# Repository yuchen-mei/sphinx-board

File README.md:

# Sphinx ASIC Test Board

Sphinx is a test board for voltage, frequency, power, and energy-efficiency characterization of a TSMC N7 ASIC. The nominal operating point is 0.75 V core supply, approximately 5 W during kernel execution, and a target clock frequency of 1 GHz. A local programmable regulator, distributed decoupling, and differential feedback at the socket provide the board-level power delivery path.

Hardware: **V2**. This package contains the current schematic project, local KiCad libraries, BOM, schematic exports, and design documentation. The [Pico controller source](../controller/README.md) is maintained alongside this package. There is no V2 PCB, completed host test application, or board measurement evidence in the current repository.

## Design files

Open [schematic/sphinx_power_v2.kicad_pro](schematic/sphinx_power_v2.kicad_pro) in KiCad 10.

| File | Contents |
|---|---|
| [Schematic PDF](schematic/exports/sphinx_power_v2.pdf) | Eleven schematic sheets |
| [XML netlist](schematic/exports/sphinx_power_v2.net.xml) | Component connections |
| [Parts catalog](schematic/bom/parts_catalog.json) | Exact parts, assembly options, and application notes |
| [Purchase list](schematic/bom/BUY_LIST.csv) | Quantities for five boards and spares |
| [Component list](schematic/bom/component_list.csv) | Schematic components and fields |
| [Documentation](docs/README.md) | Requirements, interfaces, layout constraints, and verification |
| [Maintenance](CONTRIBUTING.md) | Editing and validation procedure |

## Operating scope

The core regulator covers 0.30–1.20 V. The lower end supports low-voltage energy-efficiency measurements. The conservative continuous-current design target is 10 A. I/O operates at a fixed 1.8 V. The supported operating region is determined experimentally for each device and workload; the regulator range does not define an ASIC voltage rating.

The board uses explicit `SET` / `ON` commands to program and enable the supplies. Once a command completes, the regulator and board-powered GPIO expander retain the voltage, enable and explicit reset state while 12 V remains valid. Pico restart, USB disconnect, firmware stop or Pico removal does not change that state. The [autonomous power contract](docs/AUTONOMOUS_POWER.md) defines the hardware, recovery rules and acceptance tests. Independent protection and the STOP button remain active without Pico. DUT reset is a separate, active-high control: the local button, remote optocoupler, or an explicit Pico command asserts it. With valid VIO and no request, reset is released without depending on the Pico, power-good signals, or run-latch state.

Functionality testing runs one kernel and checks its output. Power testing runs a large back-to-back kernel loop and reads averaged voltage, current, and power after operation settles. Ordinary PG/undervoltage observations, PMBus warnings, and USB inactivity are reported without resetting or shutting down the DUT. Independent board core/I/O overvoltage and local temperature protection clear the hardware run latch. The core regulator and input eFuse also retain their own protection; a regulator-only fault can stop Core without clearing I/O. STOP and latched protective trips require a new explicit `ON`; internally latched eFuse faults can require cycling the 12 V input. Full board-power loss returns to OFF. Partial input brownouts are outside the state-retention guarantee and must be characterized; regulator and control-domain resets need not occur together.

The 10 A target still requires PCB resistance, loop stability, transient, socket/package, and sustained thermal qualification. Controller commissioning and calibration are required before unrestricted operation; a passing source-level check does not establish board readiness.

The controller follows the [startup interface](docs/RESET_AND_CONTROL.md). File checksums and verification scope are recorded in [PROVENANCE.json](PROVENANCE.json).

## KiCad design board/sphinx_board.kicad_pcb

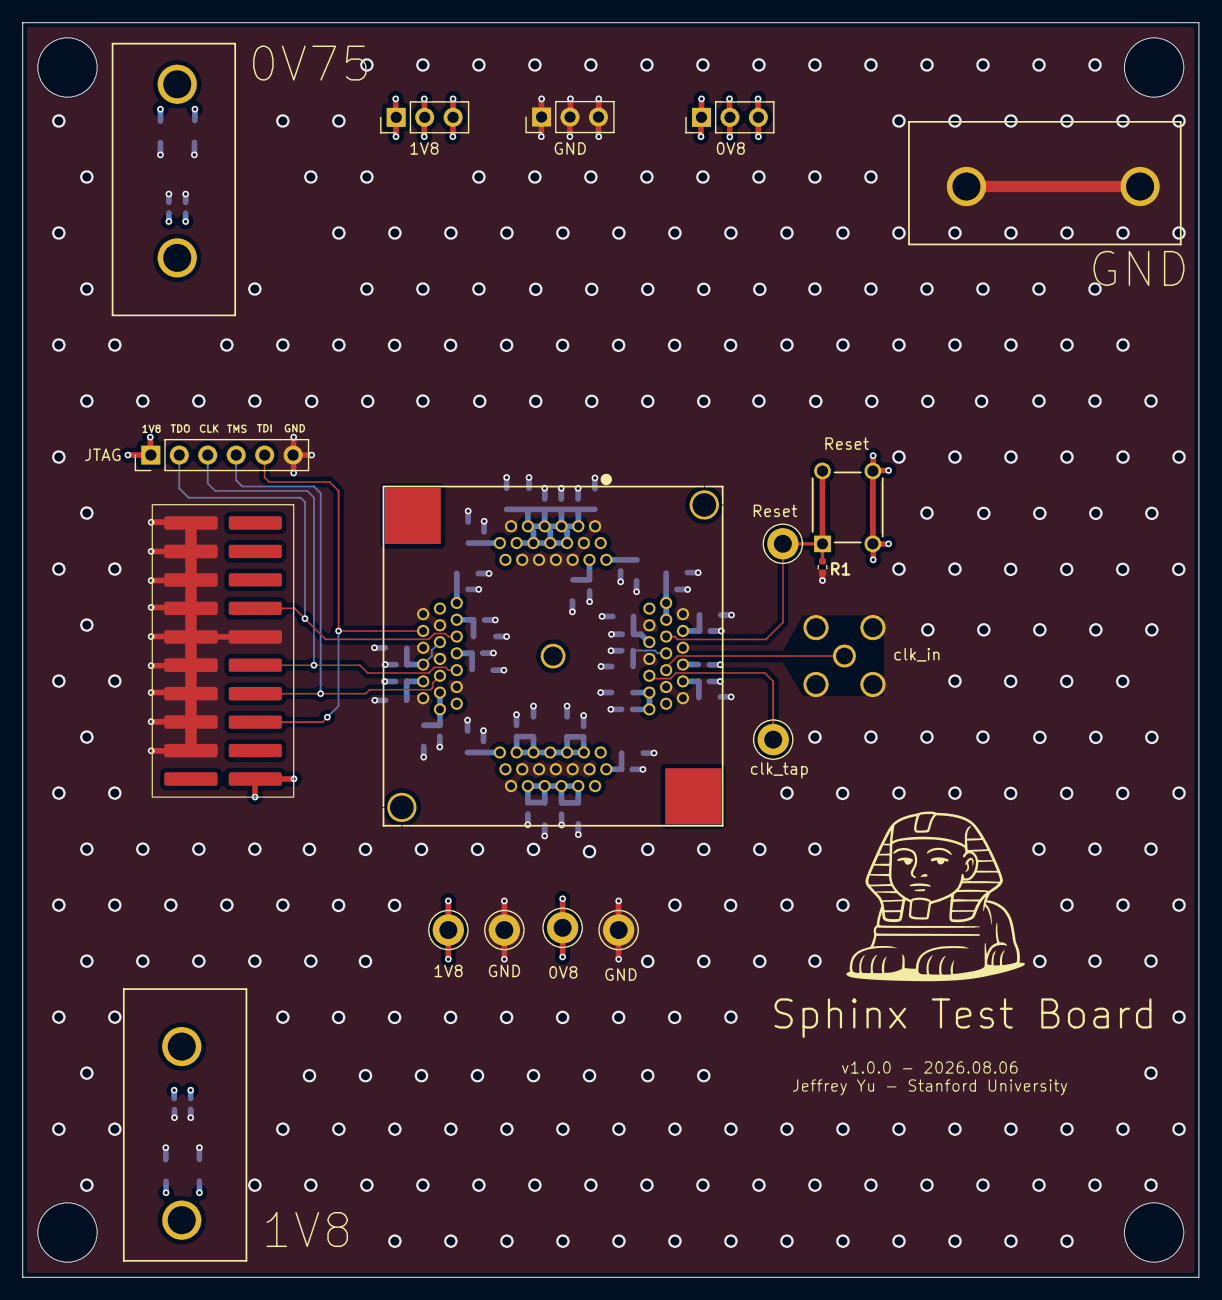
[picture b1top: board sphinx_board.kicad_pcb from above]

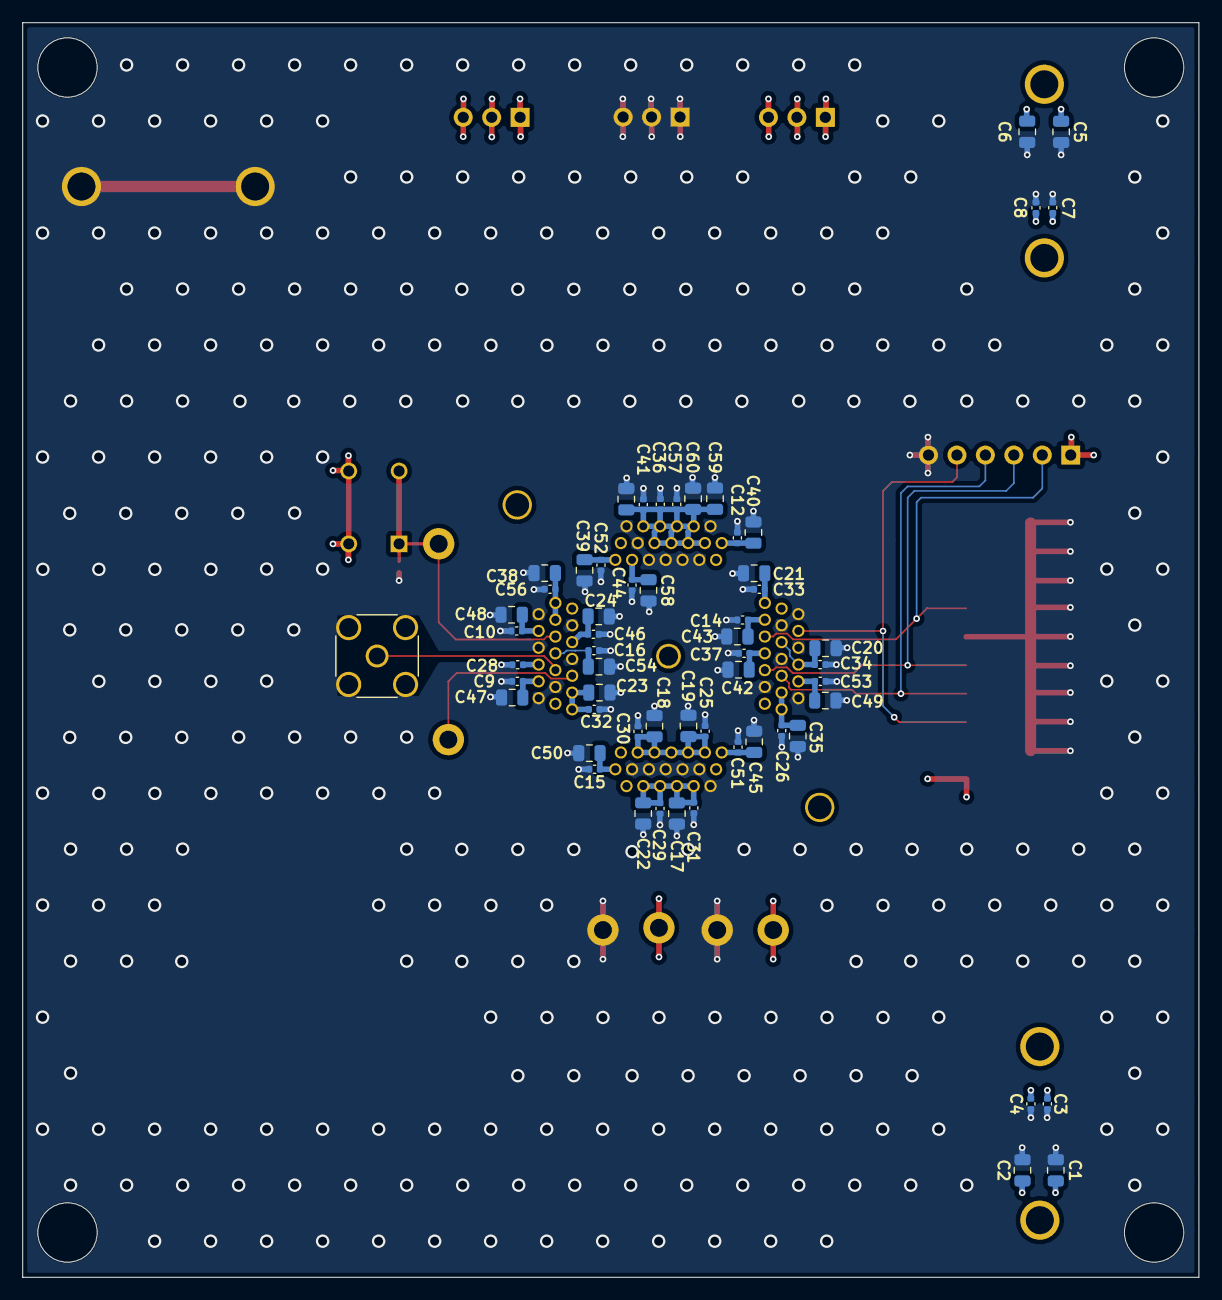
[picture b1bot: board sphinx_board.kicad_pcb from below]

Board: 6 copper layers, 105.0 x 112.0 mm, 79 parts (58 on the bottom side), 10 nets.

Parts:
C1, C2, C5, C6: 47u; C_0805_2012Metric
C3, C4, C7, C8, C9, C10, C12, C14, C15, C16, C25, C26, C28, C29, C30, C31, C32, C33, C34, C36, C37, C41, C44, C46, C51, C52, C53, C56, C57: 0.1u; C_0402_1005Metric
C17, C18, C19, C20, C21, C22, C23, C24, C35, C38, C39, C40, C42, C43, C45, C47, C48, C49, C50, C54, C58, C59, C60, C61: 1u; C_0805_2012Metric
H1, H2, H3, H4: MountingHole; MountingHole_5.3mm_M5
J1: 280-5205-01; chip_socket_new
J2: Conn_01x06_Pin; PinHeader_1x06_P2.54mm_Vertical
J5: Conn_Coaxial; SMA_Amphenol_132134-16_Vertical
J6: Conn_02x10_Counter_Clockwise; smd_jtag_connector
J7, J8, J12: Conn_01x03; PinHeader_1x03_P2.54mm_Vertical
J9, J10, J11: Conn_01x02_Socket; CONN_24.243_MTC
R1: 10k; R_0402_1005Metric
SW2: SW_MEC_5E; teco_push_button
TP2, TP3, TP4, TP5, TP6, TP7: TestPoint; TestPoint_Keystone_5010-5014_Multipurpose

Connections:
/0V75: C5.1, C6.1, C7.1, C8.1, C17.1, C18.1, C19.1, C20.1, C21.1, C22.1, C23.1, C24.1, C25.1, C26.1, C28.1, C29.1, C30.1, C31.1, C32.1, C33.1, C34.1, C35.1, C36.1, C38.1, C41.1, C44.1, C46.1, C56.1, C57.1, C58.1, C59.1, C60.1, C61.1, J1.1 (VDD), J1.8 (VDD), J1.12 (VDD), J1.17 (VDD), J1.20 (VDD), J1.24 (VDD), J1.26 (VDD), J1.27 (VDD), J1.29 (VDD), J1.30 (VDD), J1.32 (VDD), J1.33 (VDD), J1.35 (VDD), J1.36 (VDD), J1.41 (VDD), J1.44 (VDD), J1.49 (VDD), J1.53 (VDD), J1.57 (VDD), J1.60 (VDD), J1.64 (VDD), J1.66 (VDD), J1.68 (VDD), J1.69 (VDD), J1.71 (VDD), J1.72 (VDD), J1.74 (VDD), J1.75 (VDD), J1.77 (VDD), J10.1, J10.2, J12.1, J12.2, J12.3, TP3.1 (1_1)
/1V8: C1.1, C2.1, C3.1, C4.1, C9.1, C10.1, C12.1, C14.1, C15.1, C16.1, C37.1, C39.1, C40.1, C42.1, C43.1, C45.1, C47.1, C48.1, C49.1, C50.1, C51.1, C52.1, C53.1, C54.1, J1.4 (VDDPST), J1.10 (VDDPST), J1.15 (VDDPST), J1.21 (VDDPST), J1.40 (VDDPST), J1.46 (VDDPST), J1.51 (VDDPST), J1.55 (VDDPST), J1.61 (VDDPST), J1.80 (VDDPST), J2.1, J6.1, J7.1, J7.2, J7.3, J9.1, J9.2, SW2.3 (K), SW2.4 (A), TP2.1 (1_1)
/clock_tap: J1.47 (clock_tap), TP4.1 (1_1)
/jtag_TDI: J1.6 (jtag_TDI), J2.5, J6.5 (Pin_3)
/jtag_TDO: J1.7 (jtag_TDO), J2.2, J6.13 (Pin_7)
/jtag_TMS: J1.14 (jtag_TMS), J2.4, J6.7 (Pin_4)
/jtag_clk: J1.13 (jtag_TCK), J2.3, J6.9 (Pin_5)
/master_clk: J1.48 (clock), J5.1 (In)
/reset: J1.54 (reset), R1.1, SW2.1, SW2.2, TP7.1 (1_1)
GND: C1.2, C2.2, C3.2, C4.2, C5.2, C6.2, C7.2, C8.2, C9.2, C10.2, C12.2, C14.2, C15.2, C16.2, C17.2, C18.2, C19.2, C20.2, C21.2, C22.2, C23.2, C24.2, C25.2, C26.2, C28.2, C29.2, C30.2, C31.2, C32.2, C33.2, C34.2, C35.2, C36.2, C37.2, C38.2, C39.2, C40.2, C41.2, C42.2, C43.2, C44.2, C45.2, C46.2, C47.2, C48.2, C49.2, C50.2, C51.2, C52.2, C53.2, C54.2, C56.2, C57.2, C58.2, C59.2, C60.2, C61.2, J1.3 (VSS), J1.5 (VSS), J1.9 (VSS), J1.11 (VSS), J1.16 (VSS), J1.18 (VSS), J1.23 (VSS), J1.25 (VSS), J1.28 (VSS), J1.31 (VSS), J1.34 (VSS), J1.37 (VSS), J1.43 (VSS), J1.45 (VSS), J1.50 (VSS), J1.52 (VSS), J1.56 (VSS), J1.58 (VSS), J1.63 (VSS), J1.65 (VSS), J1.67 (VSS), J1.70 (VSS), J1.73 (VSS), J1.76 (VSS), J1.78 (VSS), J2.6, J5.2 (Ext), J6.4 (Pin_19), J6.6 (Pin_18), J6.8 (Pin_17), J6.10 (Pin_16), J6.11 (Pin_6), J6.12 (Pin_15), J6.14, J6.16 (Pin_13), J6.18 (Pin_12), J6.20 (Pin_11), J8.1, J8.2, J8.3, J11.1, J11.2, R1.2, TP5.1 (1_1), TP6.1 (1_1)

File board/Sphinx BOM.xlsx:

Reference | Qty | Value | DNP | Footprint | Datasheet | Manufacturer_Name | Manufacturer_Part_Number | Description | #
C1,C2,C5,C6 | 4 | 47u |  | Capacitor_SMD:C_0805_2012Metric |  |  |  | Unpolarized capacitor | 1
C3,C4,C7,C8,C9,C10,C12,C14,C15,C16,C25,C26,C28,C29,C30,C31,C32,C33,C34,C36,C37,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 | 29 | 0.1u |  | Capacitor_SMD:C_0402_1005Metric |  |  |  | Unpolarized capacitor | 2
C17,C18,C19,C20,C21,C22,C23,C24,C35,C38,C39,C40,C42,C43,C45,C47,C48,C49,C50,C54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 | 24 | 1u |  | Capacitor_SMD:C_0805_2012Metric |  |  |  | Unpolarized capacitor | 3
J2 | 1 | Conn_01x06_Pin |  | Connector_PinHeader_2.54mm:PinHeader_1x06_P2.54mm_Vertical |  |  |  | Generic connector, single row, 01x06, script generated | 4
J5 | 1 | Conn_Coaxial |  | Connector_Coaxial:SMA_Amphenol_132134-16_Vertical |  |  |  | coaxial connector (BNC, SMA, SMB, SMC, Cinch/RCA, LEMO, ...) | 5
J6 | 1 | Conn_02x10_Counter_Clockwise |  | my_footprints:smd_jtag_connector |  |  |  | Generic connector, double row, 02x10, counter clockwise pin numbering scheme (s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 | 6
J7,J8,J12 | 3 | Conn_01x03 |  | Connector_PinHeader_2.54mm:PinHeader_1x03_P2.54mm_Vertical |  |  |  | Generic connector, single row, 01x03, script generated (kicad-library-utils/sch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 | 7
J9,J10,J11 | 3 | Conn_01x02_Socket |  | my_footprints:CONN_24.243_MTC |  |  |  | Generic connector, single row, 01x02, script generated | 8
R1 | 1 | 10k |  | Resistor_SMD:R_0402_1005Metric |  |  |  | Resistor | 9
SW2 | 1 | SW_MEC_5E |  | my_footprints:teco_push_button | https://www.apem.com/medias/download/MEC_switches_serie_MULT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 |  |  | MEC 5E single pole normally-open tactile switch | 10
TP2,TP3,TP4,TP5,TP6,TP7 | 6 | TestPoint |  | TestPoint:TestPoint_Keystone_5010-5014_Multipurpose |  |  |  | test point | 11
